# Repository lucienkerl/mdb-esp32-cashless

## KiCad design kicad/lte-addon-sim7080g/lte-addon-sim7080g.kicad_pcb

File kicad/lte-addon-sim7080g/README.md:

# LTE add-on module (SIM7080G) for the WROOM-1U board

Plug-in module that gives the [MDB ESP32-S3-WROOM-1U board](../mdb_slave_esp32s3-wroom-1u/)
an LTE-M / NB-IoT uplink. It sits on the mainboard's **J2** (1×6 JTAG socket) and
reuses the proven modem circuit of the [SIM7080G board](../mdb-slave-esp32s3-sim7080g/):
SIMCom SIM7080G, Nano-SIM, U.FL antenna connector.

## Status

- Revision **1.0**, not built yet — treat the first batch as a prototype.
- 4-layer board, 50 × 27.3 mm (with a 16 × 4 mm tab carrying the header).
- ERC: 1 known item (below). DRC: 0 errors, 0 warnings, 0 unconnected; schematic and PCB in sync.
- Fabrication files for JLCPCB in [`fab/`](fab/): gerber + drill zip, `BOM_JLCPCB.csv`, `CPL_JLCPCB.csv`.

## Connector (J1, male header on the bottom)

| J1 / mainboard J2 pin | ESP32-S3 | Function on the module |
|---|---|---|
| 1 | GPIO42 (MTMS) | DETECT — 10k pull-up to 3V3, so it reads HIGH when the module is plugged in |
| 2 | GPIO41 (MTDI) | PWRKEY — GPIO high turns Q3 on and pulls PWRKEY low (“press”) |
| 3 | GPIO40 (MTDO) | ESP TX → modem UART1_RXD (level shifter Q1) |
| 4 | GPIO39 (MTCK) | modem UART1_TXD → ESP RX (level shifter Q2) |
| 5 | GND | |
| 6 | +3V3 | modem supply (VBAT) via R1 |

The pin numbers are printed next to the header on the bottom silkscreen.

## Circuit

- **Supply**: VBAT is the mainboard's 3V3 rail through R1 (0 Ω, 1206), exactly like the
  SIM7080G board. SIM7080G accepts 2.7–4.8 V and only does LTE-M / NB-IoT (no 2G bursts),
  so the AP63201 on the mainboard (2 A) has enough headroom. C1 (220 µF low-ESR tantalum),
  C2 (100 µF), C3 (22 µF) and C4–C6 (100 nF / 33 pF / 10 pF) sit next to the VBAT pins and
  carry the TX bursts. Remove R1 and bridge it with an ammeter to measure the modem current.
  A local buck regulator from the MDB supply was considered and dropped: it does not fit next
  to the modem at this size, and an extra supply cable would not clear the case lid.
- **UART**: 3.3 V ↔ 1.8 V (VDD_EXT) level shifting with two MMBT3904 (Q1/Q2) and pull-ups
  R2–R5, the same topology as the SIM7080G board.
- **PWRKEY**: Q3 with R6 (4.7k base) and R7 (4.7k base-to-GND, keeps the modem off while
  GPIO41 floats during ESP reset). Polarity matches `MODEM_PWRKEY_INVERTED = 1`.
- **Nano-SIM**: JAE SF72S006, 22 Ω series resistors R12–R14, C7 on SIM_VDD.
- **Antenna**: 50 Ω line on F.Cu over the In1 ground plane (0.36 mm, JLC 4-layer stack-up),
  pi match R15 (0 Ω) + C8/C9 (not fitted), Hirose U.FL (J3). Use a U.FL → SMA bulkhead pigtail;
  the case needs a second SMA hole next to the WiFi antenna.
- **Status**: green network LED (D1, NETLIGHT via Q4), test points STATUS, VBAT, GND.
- GNSS and USB of the SIM7080G are not used.

## Assembly

- Solder a **1×6 male pin header on the bottom**, pins pointing down. On the mainboard J2
  takes a standard 8.5 mm female socket, which puts the module about 11 mm above the mainboard;
  the tallest part on top (SIM holder / modem) stays well under the 19 mm lid clearance.
- The outline keeps clear of the mainboard's tall parts (checked against their courtyards and
  silkscreen body outlines): about 0.6 mm to J1 (RFID cable), 0.4 mm to the I2C connector J3,
  1.0 mm to the custom-input terminal P2 (the top-right notch is for it), 0.85 mm to the screw terminals P3/P5/P6 along
  the bottom edge, 1.5 mm to the MDB connector. The buzzer sits under the module
  (3 mm tall, so 8 mm of air), which makes it a little quieter.
- H1/H2 (M2) take optional 11 mm nylon spacers resting on the mainboard; both land on bare
  board (H2 next to R18, clear of it with a 4 mm spacer).
- The modem pads carry via-in-pad ground vias: order **plugged / tented vias** (JLC “epoxy
  filled and capped”), otherwise solder wicks into them.
- J1, the test points and the mounting holes are not in the CPL (hand soldered / no part).

## Ordering at JLCPCB (PCB + assembly)

1. **PCB:** upload `fab/lte-addon-sim7080g_gerber_JLCPCB.zip`. Settings: 4 layers, 1.6 mm,
   impedance control with the JLC04161H-7628 stack-up (the RF line is sized for it), via
   covering **"Epoxy filled & capped"** (via-in-pad under the modem), surface finish ENIG
   recommended for the LCC modem pads.
2. **Assembly:** PCBA on the **top side** only, upload `fab/BOM_JLCPCB.csv` and
   `fab/CPL_JLCPCB.csv`. Every part carries its LCSC number. The SIM7080G (C2943992), the SIM
   holder (C2977286), the U.FL (C88373) and the 1210/tantalum caps are extended parts: check
   stock, or pre-order them into your JLC parts library before ordering.
3. In the placement preview check the rotation of U1 (pin-1 marker), C1 (tantalum polarity),
   D1 and the four SOT-23s; JLC's library origins sometimes differ from KiCad's.
4. C8/C9 (antenna match) stay unfitted. Solder J1 (1×6 male header, bottom side, pins down)
   by hand.

## Firmware

`mdb-slave-esp32s3` detects the module at boot: on the WROOM-1U board it reads GPIO42 with the
internal pull-down; HIGH selects GPIO39/40/41 as modem pins (`modem_set_pins()`) and the
normal cellular boot runs. Without the module the modem probe stays off, as before.

## Known ERC item

`power_pin_not_driven` on the SIM holder's VCC (J2 pin C1): SIM_VDD is driven by the modem's
SIM_VDD output, which the vendor symbol marks as a power pin. A PWR_FLAG would clash with that
output pin, so the item is left and only documented here.

## Regenerating

The design is generated from one source: [`scripts/design.py`](scripts/design.py) holds every part
and its pin-to-net map. Edit it, not the KiCad files. With KiCad 9 (e.g. the `kicad/kicad:9.0`
Docker image, which has `kicad-cli` and the pcbnew Python module):

```bash
cd kicad/lte-addon-sim7080g
docker run --rm -u 0 -v "$PWD":/p -w /p kicad/kicad:9.0 bash scripts/build.sh   # sch, place, route, DRC
docker run --rm -u 0 -v "$PWD":/p -w /p kicad/kicad:9.0 bash scripts/fab.sh     # gerbers, BOM, CPL, renders
```

| Script | Does |
|---|---|
| `gen_sch.py` | schematic from `design.py` |
| `gen_pcb.py place` / `finish` | outline, placement (mainboard coordinates, so J1 lands on J2), RF line, zones, silkscreen |
| `route.py` | grid router for all other nets plus ground fan-out and stitching |
| `fab.sh` / `jlc.py` | JLCPCB outputs |

The SIM7080G symbol and footprint (`lib/`) come from `../mdb-slave-esp32s3-sim7080g/SIM7080G.zip`.
The 3D renders show bare pads where the Docker image has no 3D models.

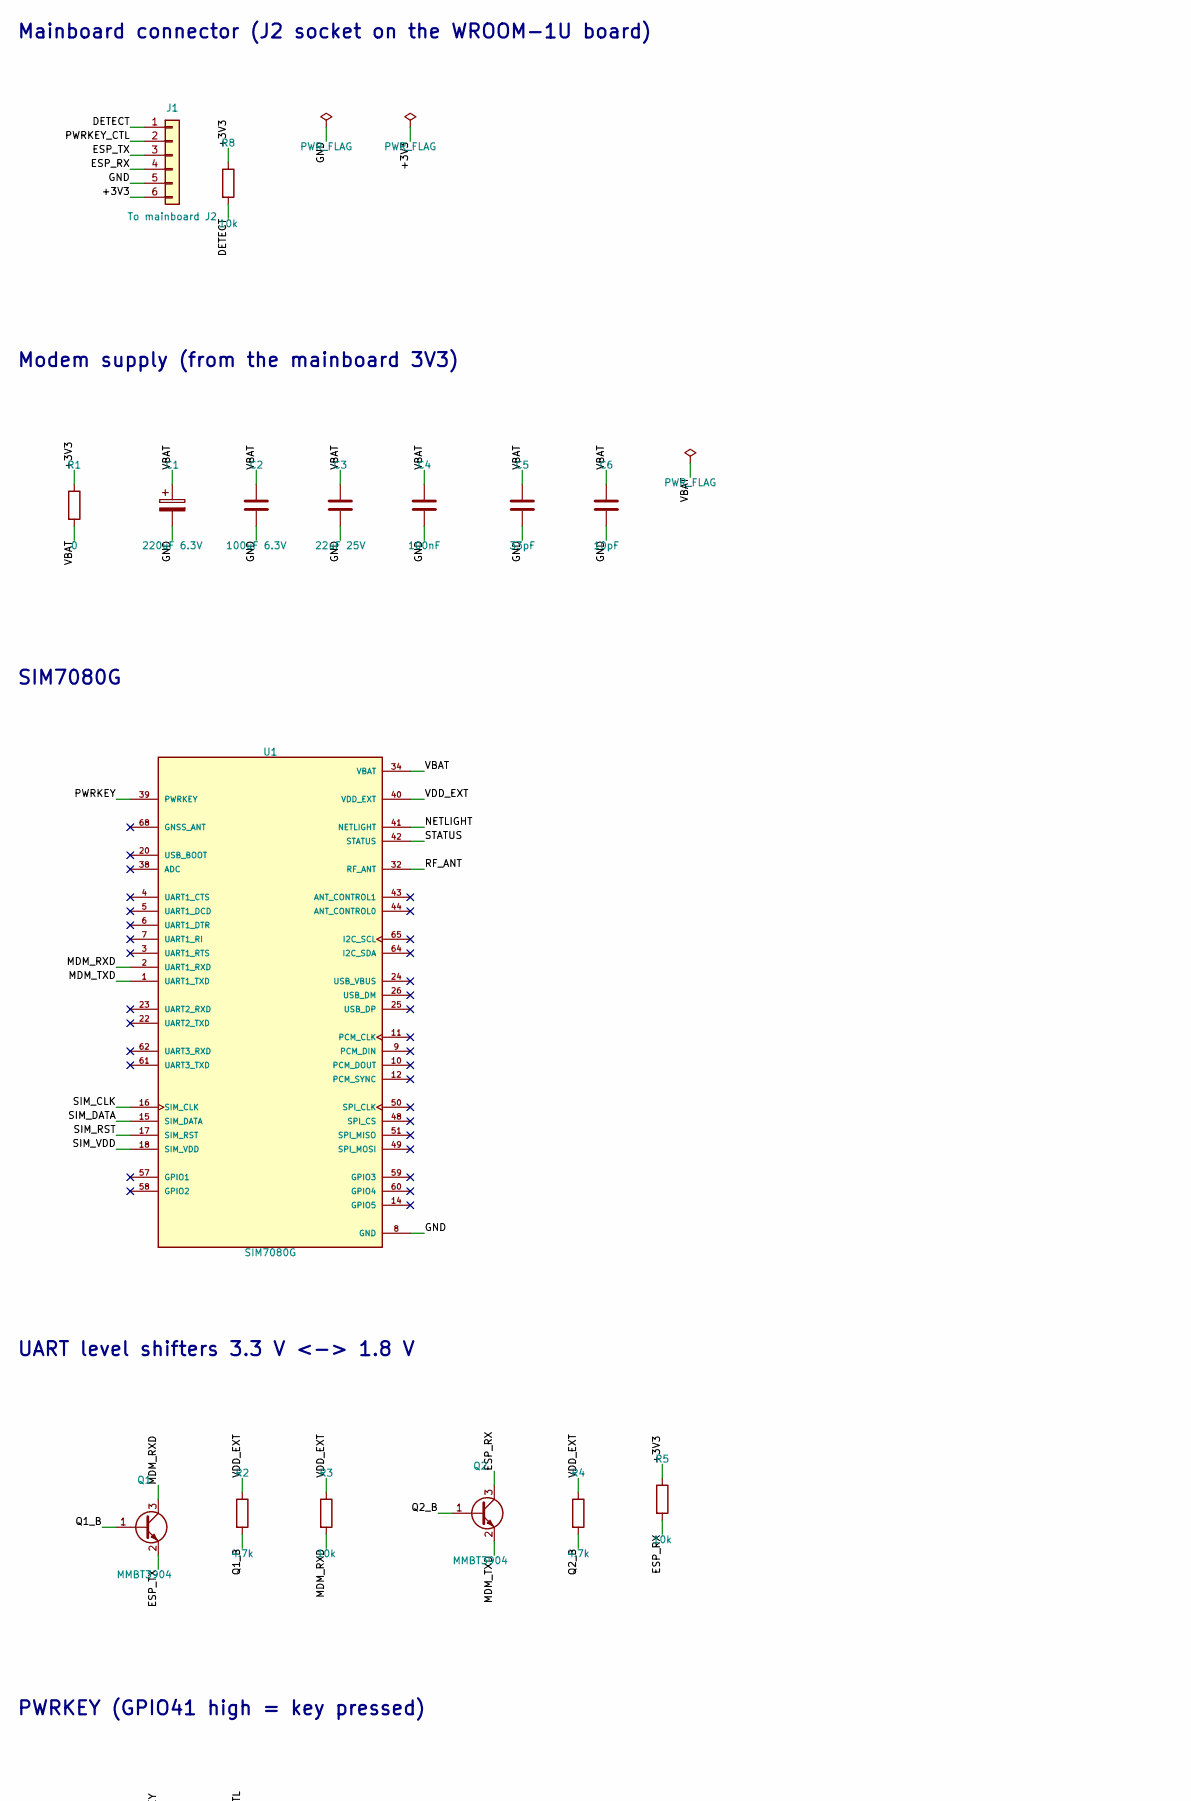
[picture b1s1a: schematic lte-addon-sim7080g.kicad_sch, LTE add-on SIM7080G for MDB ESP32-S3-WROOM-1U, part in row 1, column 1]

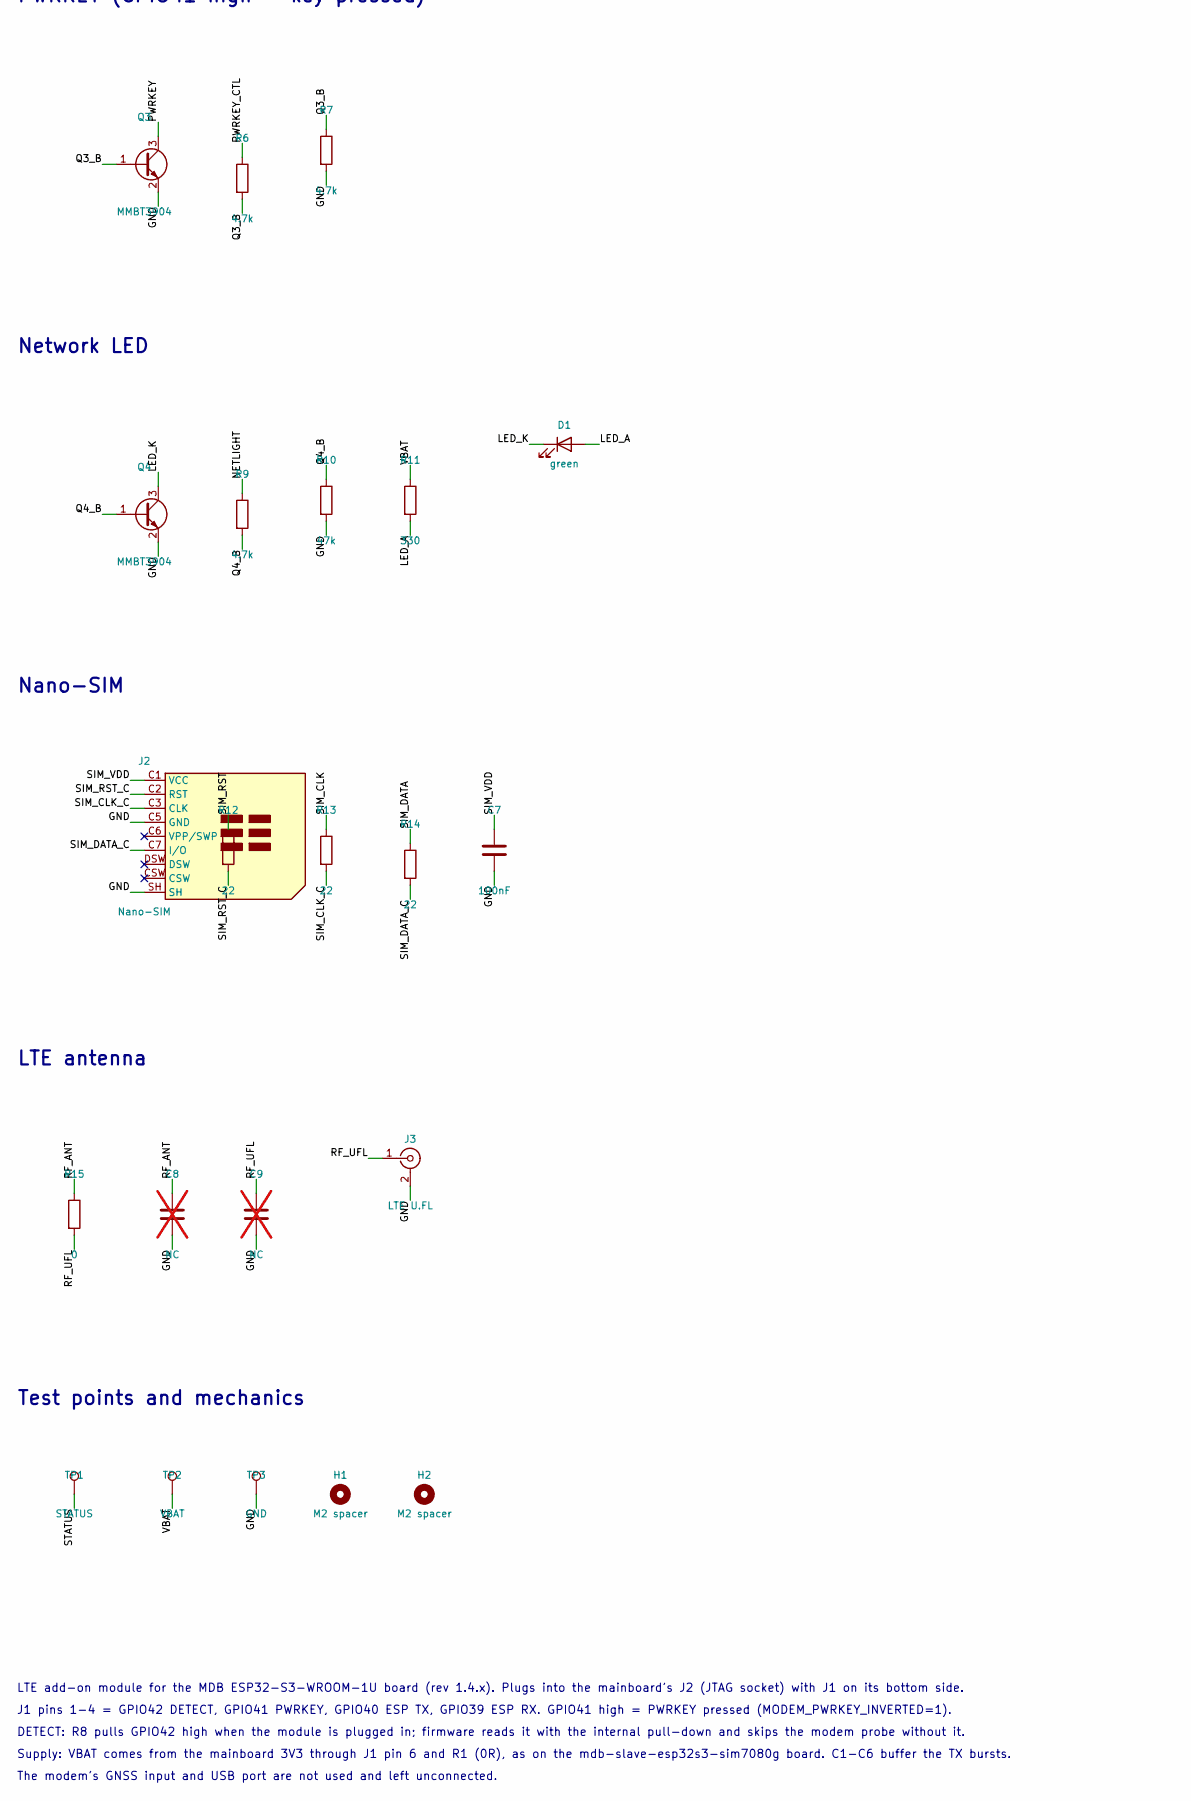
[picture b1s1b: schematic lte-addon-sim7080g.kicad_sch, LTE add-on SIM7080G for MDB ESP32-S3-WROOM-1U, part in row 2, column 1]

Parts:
C1: 220uF 6.3V; CP_EIA-3528-21_Kemet-B; MPN Kemet T520B227M006ATE070 (low ESR); LCSC C600584
C2: 100uF 6.3V; C_1210_3225Metric; LCSC C49066
C3: 22uF 25V; C_0805_2012Metric; LCSC C45783
C4, C7: 100nF; C_0603_1608Metric; LCSC C14663
C5: 33pF; C_0603_1608Metric; LCSC C1663
C6: 10pF; C_0603_1608Metric; LCSC C1634
C8, C9: NC; C_0603_1608Metric; not fitted
D1: green; LED_0603_1608Metric; LCSC C12624
H1, H2: M2 spacer; MountingHole_2.2mm_M2
J1: To mainboard J2; PinHeader_1x06_P2.54mm_Vertical; MPN Male pin header 1x6 2.54 mm, mounted on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
J2: Nano-SIM; JAE_SIM_Card_SF72S006; MPN JAE SF72S006VBDR2500; LCSC C2977286
J3: LTE U.FL; U.FL_Hirose_U.FL-R-SMT-1_Vertical; MPN Hirose U.FL-R-SMT-1; LCSC C88373
Q1, Q2, Q3, Q4: MMBT3904; SOT-23; LCSC C20526
R1: 0; R_1206_3216Metric; LCSC C17888
R2, R4, R6, R7, R9: 4.7k; R_0603_1608Metric; LCSC C23162
R3, R5, R8: 10k; R_0603_1608Metric; LCSC C25804
R10: 47k; R_0603_1608Metric; LCSC C25819
R11: 330; R_0603_1608Metric; LCSC C23138
R12, R13, R14: 22; R_0603_1608Metric; LCSC C23345
R15: 0; R_0603_1608Metric; LCSC C21189
TP1: STATUS; TestPoint_Pad_D1.0mm
TP2: VBAT; TestPoint_Pad_D1.0mm
TP3: GND; TestPoint_Pad_D1.0mm
U1: SIM7080G; XCVR_SIM7080G; MPN SIMCom SIM7080G; LCSC C2943992

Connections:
/+3V3: J1.6, R1.1, R5.1, R8.1
/DETECT: J1.1, R8.2
/ESP_RX: J1.4, Q2.3 (C), R5.2
/ESP_TX: J1.3, Q1.2 (E)
/LED_A: D1.2 (A), R11.2
/LED_K: D1.1 (K), Q4.3 (C)
/MDM_RXD: Q1.3 (C), R3.2, U1.2 (UART1_RXD)
/MDM_TXD: Q2.2 (E), U1.1 (UART1_TXD)
/NETLIGHT: R9.1, U1.41 (NETLIGHT)
/PWRKEY: Q3.3 (C), U1.39 (PWRKEY)
/PWRKEY_CTL: J1.2, R6.1
/Q1_B: Q1.1 (B), R2.2
/Q2_B: Q2.1 (B), R4.2
/Q3_B: Q3.1 (B), R6.2, R7.1
/Q4_B: Q4.1 (B), R9.2, R10.1
/RF_ANT: C8.1, R15.1, U1.32 (RF_ANT)
/RF_UFL: C9.1, J3.1 (In), R15.2
/SIM_CLK: R13.1, U1.16 (SIM_CLK)
/SIM_CLK_C: J2.C3 (CLK), R13.2
/SIM_DATA: R14.1, U1.15 (SIM_DATA)
/SIM_DATA_C: J2.C7 (I/O), R14.2
/SIM_RST: R12.1, U1.17 (SIM_RST)
/SIM_RST_C: J2.C2 (RST), R12.2
/SIM_VDD: C7.1, J2.C1 (VCC), U1.18 (SIM_VDD)
/STATUS: TP1.1, U1.42 (STATUS)
/VDD_EXT: R2.1, R3.1, R4.1, U1.40 (VDD_EXT)
GND: C1.2, C2.2, C3.2, C4.2, C5.2, C6.2, C7.2, C8.2, C9.2, J1.5, J2.C5 (GND), J2.SH, J3.2 (Ext), Q3.2 (E), Q4.2 (E), R7.2, R10.2, TP3.1, U1.8 (GND), U1.13 (GND), U1.19 (GND), U1.21 (GND), U1.27 (GND), U1.30 (GND), U1.31 (GND), U1.33 (GND), U1.36 (GND), U1.37 (GND), U1.45 (GND), U1.63 (GND), U1.66 (GND), U1.67 (GND), U1.69 (GND), U1.70 (GND), U1.71 (GND), U1.72 (GND), U1.73 (GND), U1.74 (GND), U1.75 (GND), U1.76 (GND), U1.77 (GND)
VBAT: C1.1, C2.1, C3.1, C4.1, C5.1, C6.1, R1.2, R11.1, TP2.1, U1.34 (VBAT), U1.35 (VBAT)

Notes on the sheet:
Mainboard connector (J2 socket on the WROOM-1U board)
Modem supply (from the mainboard 3V3)
SIM7080G
UART level shifters 3.3 V <-> 1.8 V
PWRKEY (GPIO41 high = key pressed)
Network LED
Nano-SIM
LTE antenna
Test points and mechanics
LTE add-on module for the MDB ESP32-S3-WROOM-1U board (rev 1.4.x). Plugs into the mainboard's J2 (JTAG socket) with J1 on its bottom side.
J1 pins 1-4 = GPIO42 DETECT, GPIO41 PWRKEY, GPIO40 ESP TX, GPIO39 ESP RX. GPIO41 high = PWRKEY pressed (MODEM_PWRKEY_INVERTED=1).
DETECT: R8 pulls GPIO42 high when the module is plugged in; firmware reads it with the internal pull-down and skips the modem probe without it.
Supply: VBAT comes from the mainboard 3V3 through J1 pin 6 and R1 (0R), as on the mdb-slave-esp32s3-sim7080g board. C1-C6 buffer the TX bursts.
The modem's GNSS input and USB port are not used and left unconnected.

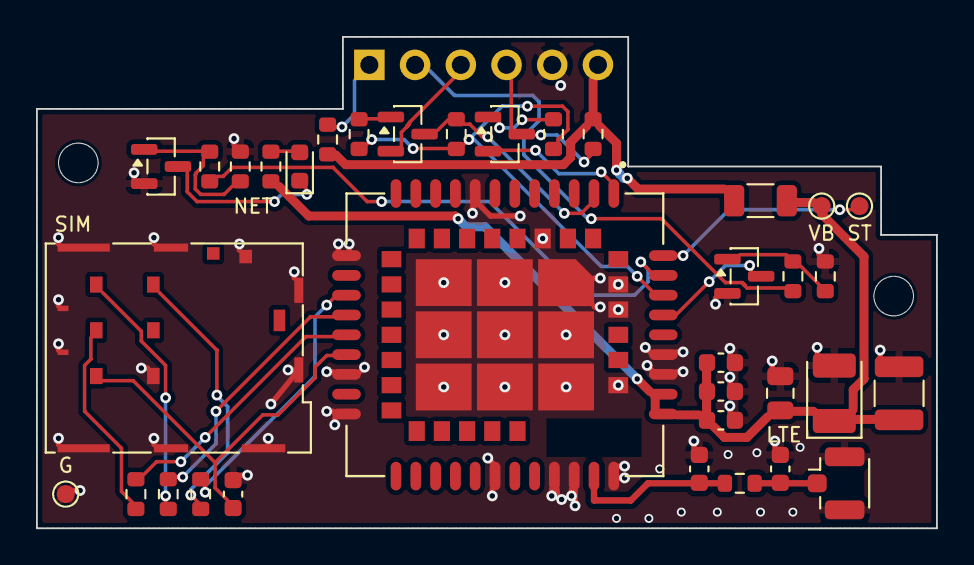
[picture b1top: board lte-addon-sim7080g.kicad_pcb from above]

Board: 4 copper layers, 50.0 x 27.3 mm, 38 parts (1 on the bottom side), 28 nets.

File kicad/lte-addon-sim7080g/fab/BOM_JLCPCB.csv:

Comment,Designator,Footprint,LCSC Part #,MPN / note,Quantity
220uF 6.3V,C1,CP_EIA-3528-21_Kemet-B,C600584,Kemet T520B227M006ATE070 (low ESR),1
100uF 6.3V,C2,C_1210_3225Metric,C49066,,1
22uF 25V,C3,C_0805_2012Metric,C45783,,1
100nF,"C4,C7",C_0603_1608Metric,C14663,,2
33pF,C5,C_0603_1608Metric,C1663,,1
10pF,C6,C_0603_1608Metric,C1634,,1
green,D1,LED_0603_1608Metric,C12624,,1
Nano-SIM,J2,JAE_SIM_Card_SF72S006,C2977286,JAE SF72S006VBDR2500,1
LTE U.FL,J3,U.FL_Hirose_U.FL-R-SMT-1_Vertical,C88373,Hirose U.FL-R-SMT-1,1
MMBT3904,"Q1,Q2,Q3,Q4",SOT-23,C20526,,4
0,R1,R_1206_3216Metric,C17888,,1
4.7k,"R2,R4,R6,R7,R9",R_0603_1608Metric,C23162,,5
10k,"R3,R5,R8",R_0603_1608Metric,C25804,,3
47k,R10,R_0603_1608Metric,C25819,,1
330,R11,R_0603_1608Metric,C23138,,1
22,"R12,R13,R14",R_0603_1608Metric,C23345,,3
0,R15,R_0603_1608Metric,C21189,,1
SIM7080G,U1,XCVR_SIM7080G,C2943992,SIMCom SIM7080G,1

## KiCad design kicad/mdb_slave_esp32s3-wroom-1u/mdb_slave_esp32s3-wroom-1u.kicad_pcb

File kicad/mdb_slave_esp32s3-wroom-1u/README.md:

# MDB ESP32-S3 Cashless Module

Custom PCB adding cashless payment and telemetry to vending machines via the **MDB (Multi-Drop Bus)** protocol. Built around an **ESP32-S3-WROOM-1U** module with external antenna. Designed in KiCad 10.

Target platform: any vending machine equipped with an MDB bus. Backend (Supabase + MQTT + Nuxt, Dockerized) is out of scope for this repo.

Base reference: [lucienkerl/mdb-esp32-cashless](https://github.com/lucienkerl/mdb-esp32-cashless).

## Status

- Schematic: complete — ERC has 4 minor housekeeping items left (floating power symbols / an
  unconnected test pad, no real connectivity impact)
- PCB layout: routed, 4-layer board, 149.8 × 38.5 mm — schematic and PCB are in sync (all
  references renumbered and re-synced in rev1.4, including the previously-orphaned 1-Wire
  pull-up R4)
- Revision: **1.4.1** (R26/R28 changed from 10KΩ to 1KΩ)
- Gerbers in `gerber_to_order/` (JLCPCB, PCBWay) reflect the current board

## Overview

The board sits between the vending machine's MDB bus and a cashless payment terminal / telemetry stack. It reads and drives the machine's MDB peripherals, exposes auxiliary sensor and actuator interfaces (1-Wire, I2C, relays, custom digital inputs), and connects to WiFi for backend communication.

Key design decisions:

- **ESP32-S3-WROOM-1U-N16R2** module (16MB flash / 2MB PSRAM) with external u.FL antenna, chosen over a bare ESP32-S3 die because vending machine enclosures are often metal and block internal WiFi.
- **4-layer PCB**, for a dedicated ground/power plane structure and better EMI control around the switching regulator and MDB interface.
- All field connectors placed at the board edge for easy wiring and to fit inside a 3D-printed enclosure.
- Physical separation between the MDB (isolated, high-voltage) side and the logic side, matching the optocoupler isolation barrier in the schematic.

## Functional blocks

**MCU — U1**
ESP32-S3-WROOM-1U-N16R2, with EN/BOOT reset circuit (buttons B1/B2, pull-ups R1/R2/R10, decoupling C1–C3). Onboard WS2812B-compatible RGB status LED (LED1, driven by GPIO21).

**Power**
- F2: PTC resettable fuse on the incoming MDB-side supply
- U8: AP63201WU-7 buck converter, input 3.8V–32V, output 3.3V — **adjustable-output part** (rev1.4, replaces the fixed-output AP63203QWU-7), set by an external feedback divider: R23 (196kΩ, top) / R24 (62kΩ, bottom), with C19 (100pF) as feed-forward capacitor across R23
- C6 (10µF input), C7 (100nF bootstrap), C8/C9 (2×22µF output), L1 (3.3µH inductor)
- Switching loop (U8–L1–output) kept as compact as possible — primary EMI concern

**USB-C — USBC1**
USB 2.0 receptacle for programming/debug, with D6 Schottky diode against VBUS backfeed and R21/R22 CC pull-downs.

**MDB interface — H1**
2×3 connector. Galvanically isolated via U5/U6 (TLP785 optocouplers, DIP-4) on TX (GPIO4) and RX (GPIO5), with D2/D3 and associated pull-up/series resistors. F1 is the PTC resettable fuse on the incoming MDB-side supply.

**Relay outputs — P8, P9** *(added rev1.3)*
Two 15A-class SPDT relays (K2, K3 — SRD-03VDC-SL-C, 3V coil on the +3V3 rail), each output exposed as a 3-pin COM/NO/NC screw terminal. Each coil is driven low-side by an MMBT3904 transistor (Q2/Q3) with a 1N4148WS flyback diode (D4/D5), itself switched through a TLP785 optocoupler (U3/U4, SMD-4) for GPIO isolation:
- P8: Relay #1 — K2 / Q2 / U3, driven from GPIO1
- P9: Relay #2 — K3 / Q3 / U4, driven from GPIO2

⚠️ Note (intentional design choice): with the current TLP785 pull-up/pull-down arrangement, drive logic is inverted (GPIO low, or floating at boot, = relay energized; GPIO high = relay de-energized). This matches this board's firmware. If you reuse this design, or adapt a different firmware to it, update the GPIO drive logic accordingly — or flip the pull-up/pull-down if a fail-safe de-energized boot default is required.

**1-Wire buses — P4, P5, P6**
Two 1-Wire interfaces plus a spare/parallel header, each with a pull-up resistor:
- P6: bus #1 (GPIO15)
- P5: bus #2 (GPIO16)
- P4: spare header on bus #1 (GPIO15)

**Custom digital inputs — P1, P2, P3**
Three screw-terminal inputs with pull-up resistors: P1 (GPIO6), P2 (GPIO17), P3 (GPIO18).

**I2C — J3**
JST XH 1×4 connector with pull-ups, SCL on GPIO11, SDA on GPIO10.

**Debug / programming**
- J1: UART debug header (1×6) — EN, TXD, RXD, IO0, GND, +3V3
- J2: JTAG header (1×6) — MTMS, MTDI, MTDO, MTCk, GND, +3V3

**Other**
- TH1: NTC thermistor input (GPIO7)
- BUZZER1: buzzer, driven by GPIO12 through Q1
- H2–H5: mounting holes
- H6–H10: test/probe pads (H8 taps the WS2812B LED1 data-out, H10 the buzzer driver)
- GPIO3: reserved for firmware-based PCB/board detection

## Connectors summary

| Ref | Function | Type |
|---|---|---|
| USBC1 | USB-C (program/debug) | USB2.0 16P receptacle |
| J1 | UART debug | 1×6 pin header |
| J2 | JTAG | 1×6 pin header |
| J3 | I2C | 1×4 JST XH |
| P1, P2, P3 | Custom digital inputs (×3) | 3-pin screw terminal, 5.08mm |
| P4, P5, P6 | 1-Wire buses (bus #1 spare, bus #2, bus #1) | 3-pin screw terminal, 5.08mm |
| P8 | Relay #1 output (COM/NO/NC) | 3-pin screw terminal, 5.08mm |
| P9 | Relay #2 output (COM/NO/NC) | 3-pin screw terminal, 5.08mm |
| H1 | MDB bus | 2×3 connector, isolated |

## Repository structure

```
mdb_slave_esp32s3-wroom-1u/
├── mdb_slave_esp32s3-wroom-1u.kicad_pro   KiCad project
├── mdb_slave_esp32s3-wroom-1u.kicad_sch   Schematic
├── mdb_slave_esp32s3-wroom-1u.kicad_pcb   PCB layout (routed, rev 1.4.1)
├── LICENSE                                CERN-OHL-S v2
├── gerber_to_order/                       Fabrication Gerbers per vendor (JLCPCB, PCBWay) — versioned
├── bom/ibom.html                          Interactive BOM (InteractiveHtmlBom export) — versioned
└── production/                            BOM, CPL, netlist (generated locally, not versioned)
```

The `.kicad_pro` / `.kicad_sch` / `.kicad_pcb` files, this README, `LICENSE`, `gerber_to_order/`,
and `bom/ibom.html` are version-controlled — see `.gitignore`.

## Browsing the board without KiCad

Open `bom/ibom.html` in any browser for an interactive BOM: it highlights each component on the
PCB (top/bottom view) when selected, lists references/values/footprints, and supports search and
filtering — useful for assembly checks or reviewing the design without installing KiCad.

## Tools

- KiCad 10.0.4
- JLCPCB / PCBWay for fabrication, assembly, and component sourcing

## License

[CERN-OHL-S v2](https://choosealicense.com/licenses/cern-ohl-s-2.0/) — see `LICENSE`.

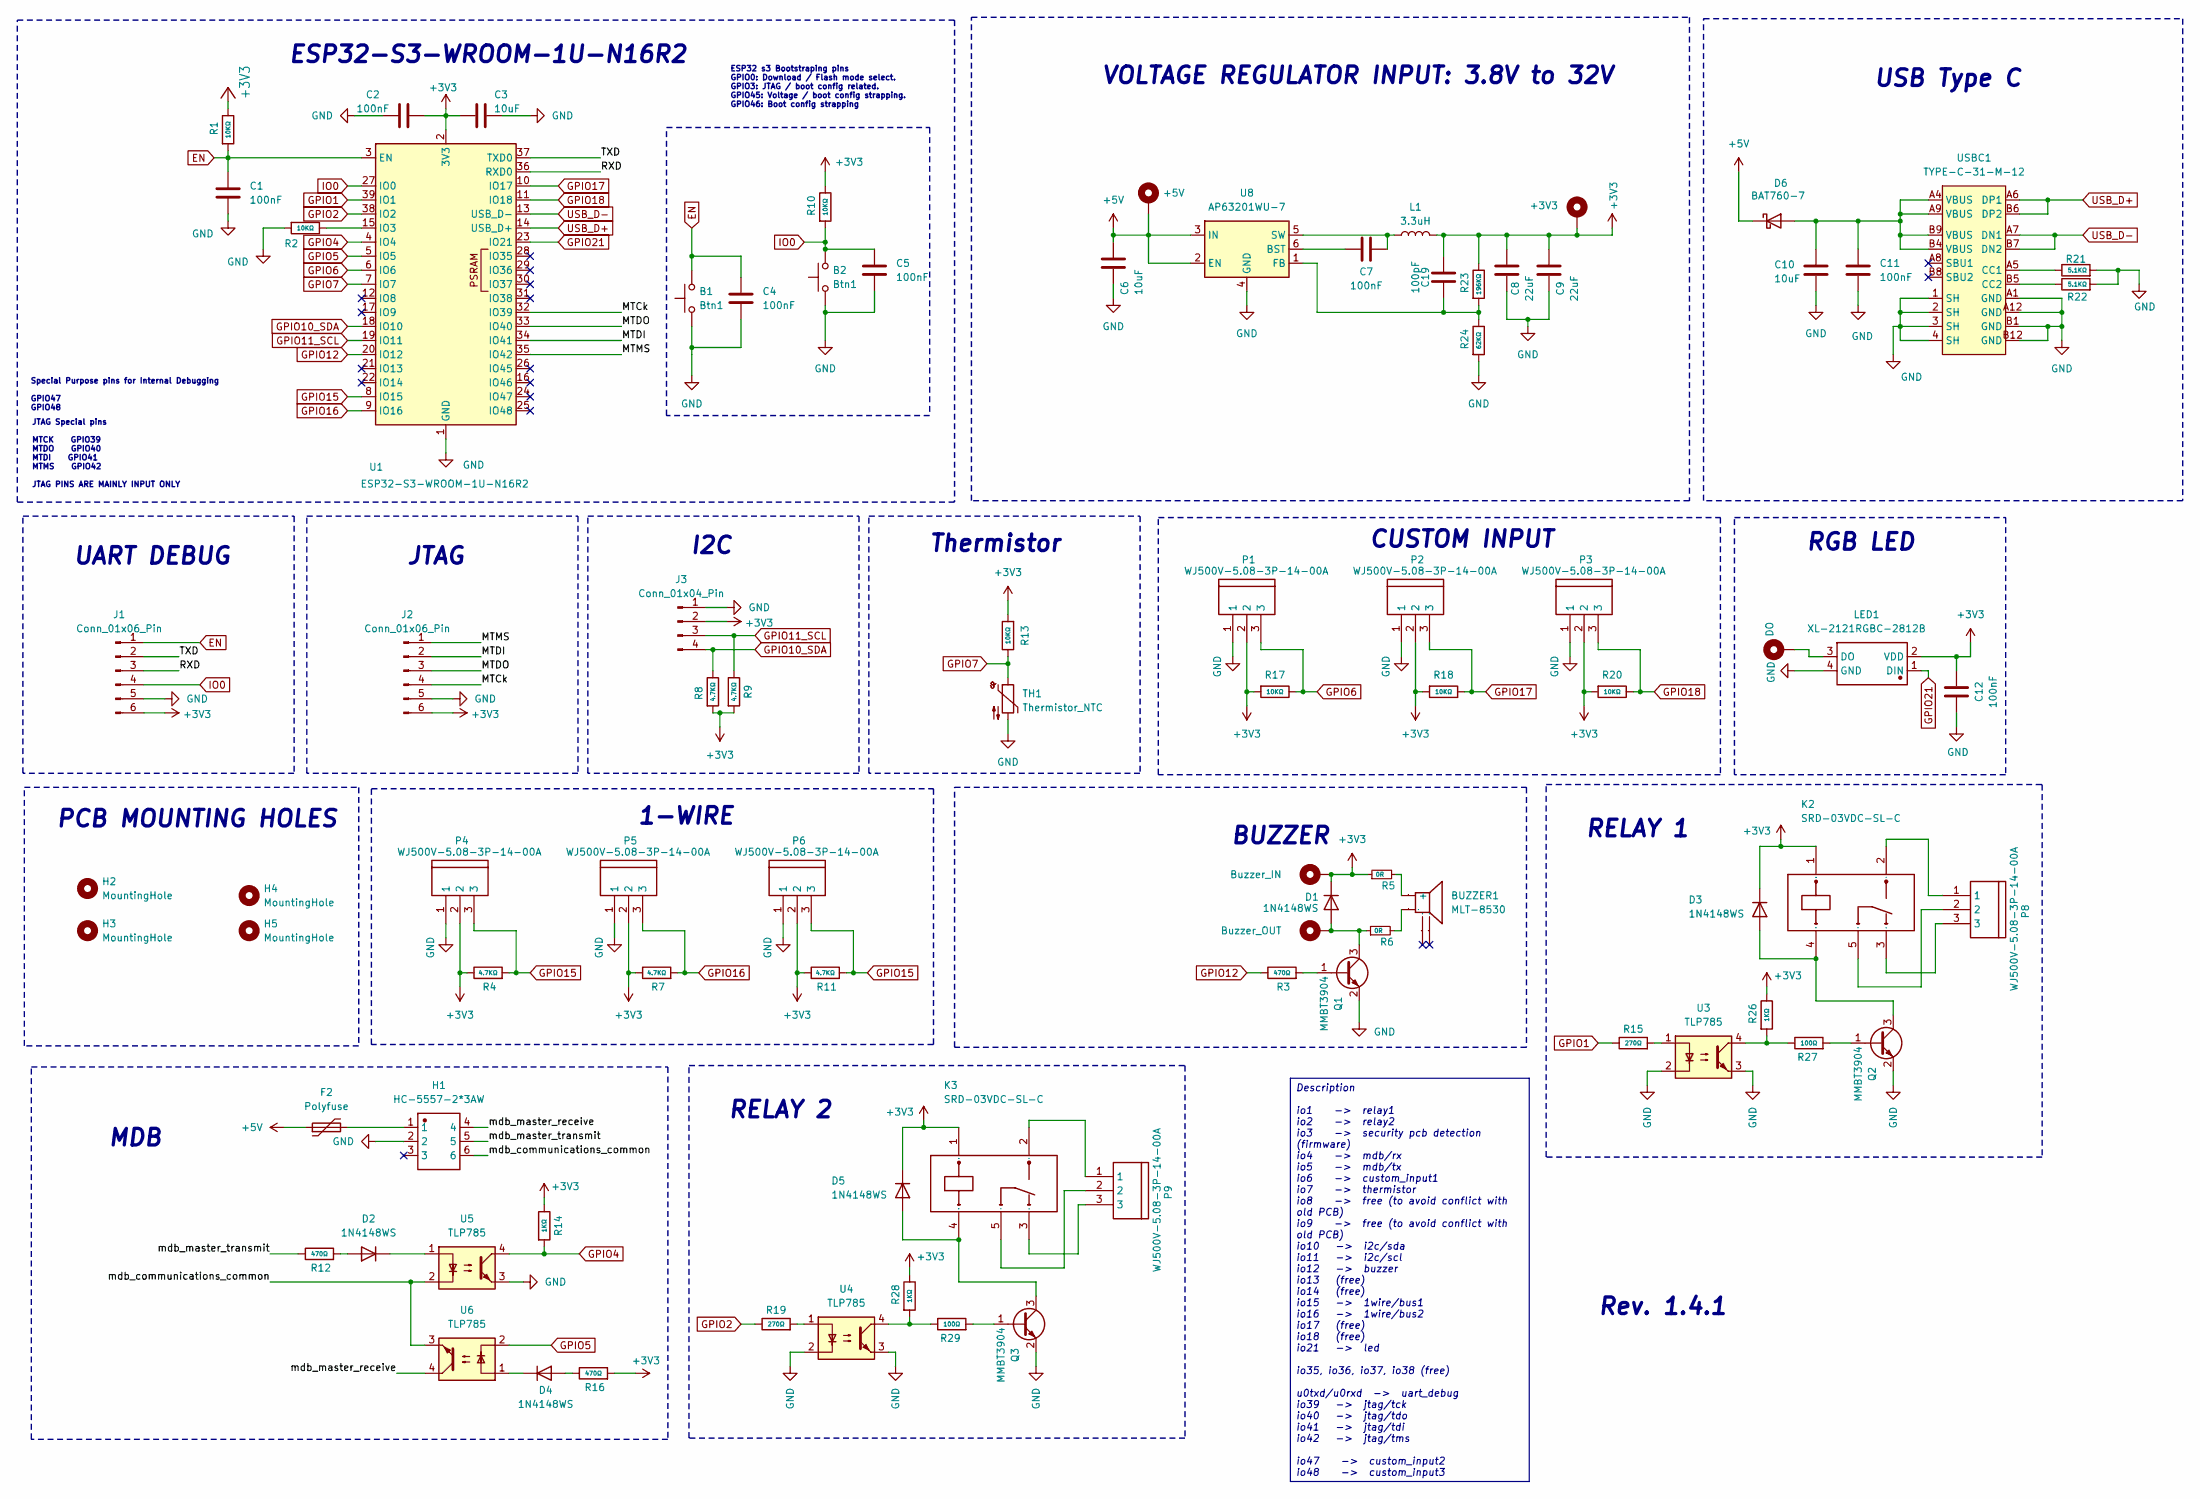
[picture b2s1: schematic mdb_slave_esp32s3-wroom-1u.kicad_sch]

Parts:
B1, B2: Btn1; KEY-SMD_B3U-1000PM; MFR.Part # B3U-1000P; LCSC C231329
BUZZER1: MLT-8530; BUZ-SMD_4P-L8.5-W8.5-P8.50-BR_C94599; MFR.Part # MLT-8530; LCSC C94599
C1, C2, C4, C5, C7, C11, C12: 100nF; C_0603_1608Metric; MFR.Part # CC0603KRX7R9BB104; LCSC C14663
C3, C6, C10: 10uF; C_0603_1608Metric; MFR.Part # CL10A106KP8NNNC; LCSC C19702
C8, C9: 22uF; C_0603_1608Metric; MFR.Part # CL10A226MQ8NRNC; LCSC C59461
C19: 100pF; C_0603_1608Metric; MFR.Part # CL10C101JB8NNNC; LCSC C14858
D1, D2, D3, D4, D5: 1N4148WS; D_SOD-323; MFR.Part # 1N4148WS; LCSC C2128
D6: BAT760-7; D_SOD-323; MFR.Part # BAT760-7; LCSC C27636120
F2: Polyfuse; C_1812_4532Metric; MFR.Part # 1812L110/33GR; LCSC C7542972
H1: HC-5557-2*3AW; CONN-TH_6P-P4.20-S5.50_5557-2X3AW_C2845788; MFR.Part # HC-5557-2*3AW; LCSC C2845788
H2, H3, H4, H5: MountingHole; MountingHole_2.7mm_M2.5_ISO7380
H6: +5V; TestPoint_Pad_D1.0mm
H7: +3V3; TestPoint_Pad_D1.0mm
H8: DO; TestPoint_Pad_D1.0mm
H9: Buzzer_IN; TestPoint_Pad_D1.0mm
H10: Buzzer_OUT; TestPoint_Pad_D1.0mm
J1, J2: Conn_01x06_Pin; PinSocket_1x06_P2.54mm_Vertical; LCSC C37208
J3: Conn_01x04_Pin; JST_XH_B4B-XH-A_1x04_P2.50mm_Vertical; MFR.Part # B4B-XH-A(LF)(SN); LCSC C144395
K2, K3: SRD-03VDC-SL-C; RELAY-TH_SRD-XXVDC-XL-C_C24585; MFR.Part # SRD-03VDC-SL-C; LCSC C24585
L1: 3.3uH; L_0603_1608Metric; MFR.Part # SDFL1608S6R8KTF; LCSC C75929
LED1: XL-2121RGBC-2812B; LED-SMD_4P-L2.1-W2.1-BR_XL-2121RGBC-WS2812B_C5349957; MFR.Part # XL-2121RGBC-2812B; LCSC C5349957
P1, P2, P3, P4, P5, P6, P8, P9: WJ500V-5.08-3P-14-00A; CONN-TH_3P-P5.00_WJ500V-5.08-3P_C72334; MFR.Part # WJ500V-5.08-03P-14-00A; LCSC C72334
Q1, Q2, Q3: MMBT3904; SOT-23; MFR.Part # MMBT3904; LCSC C916374
R1, R2, R10, R13, R17, R18, R20: 10KΩ; R_0603_1608Metric; MFR.Part # 0603WAF1002T5E; LCSC C25804
R3, R12, R16: 470Ω; R_0603_1608Metric; MFR.Part # 0603WAF4700T5E; LCSC C23179
R4, R7, R8, R9, R11: 4.7KΩ; R_0603_1608Metric; MFR.Part # 0603WAF4701T5E; LCSC C23162
R5, R6: 0R; R_0603_1608Metric_Pad0.98x0.95mm_HandSolder; MFR.Part # 0603WAF0000T5E; LCSC C21189
R14, R26, R28: 1KΩ; R_0603_1608Metric; MFR.Part # RC0603JR-071KL; LCSC C14676
R15, R19: 270Ω; R_0603_1608Metric; MFR.Part # 0603WAF2700T5E; LCSC C22966
R21, R22: 5.1KΩ; R_0603_1608Metric; MFR.Part # 0603WAF5101T5E; LCSC C23186
R23: 196KΩ; R_0603_1608Metric; MFR.Part # 0603WAF1963T5E; LCSC C22930
R24: 62KΩ; R_0603_1608Metric; MFR.Part # 0603WAF6202T5E; LCSC C23221
R27, R29: 100Ω; R_0603_1608Metric; MFR.Part # 0603WAF1000T5E; LCSC C22775
TH1: Thermistor_NTC; C_0603_1608Metric_Pad1.08x0.95mm_HandSolder; MFR.Part # NCP18XH103F03RB; LCSC C13564
U1: ESP32-S3-WROOM-1U-N16R2; WIRELM-SMD_ESP32-S3-WROOM-1U_C3013945; MFR.Part # ESP32-S3-WROOM-1U-N16R2; LCSC C3013945
U3, U4, U5, U6: TLP785; SMD-4_L4.6-W6.5-P2.54-LS10.2-BR_C45445; MFR.Part # TLP785(GB-TP6,F; LCSC C45445
U8: AP63201WU-7; TSOT-23-6; MFR.Part # AP63201WU-7; LCSC C2071044
USBC1: TYPE-C-31-M-12; USB-C_SMD-TYPE-C-31-M-12; MFR.Part # TYPE-C-31-M-12; LCSC C165948

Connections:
+3V3: C2.2, C3.2, C8.2, C9.2, C12.2, C19.1, D1.1 (K), D3.1 (K), D5.1 (K), H7.1, H9.1, J1.6, J2.6, J3.2, K2.1, K3.1, L1.2, LED1.2 (VDD), P1.2, P2.2, P3.2, P4.2, P5.2, P6.2, R1.1, R4.1, R5.1, R7.1, R8.2, R9.2, R10.1, R11.1, R13.2, R14.1, R16.2, R17.2, R18.2, R20.2, R23.1, R26.1, R28.1, U1.2 (3V3)
+5V: C6.1, D6.1 (K), F2.1, H6.1, U8.2 (EN), U8.3 (IN)
/MTCk: J2.4, U1.32 (IO39)
/MTDI: J2.2, U1.34 (IO41)
/MTDO: J2.3, U1.33 (IO40)
/MTMS: J2.1, U1.35 (IO42)
/RXD: J1.3, U1.36 (RXD0)
/TXD: J1.2, U1.37 (TXD0)
/mdb_communications_common: H1.6, U5.2, U6.3
/mdb_master_receive: H1.4, U6.4
/mdb_master_transmit: H1.5, R12.1
EN: B1.2, C1.1, C4.1, J1.1, R1.2, U1.3 (EN)
GND: B1.1, B2.1, C1.2, C2.1, C3.1, C4.2, C5.2, C6.2, C8.1, C9.1, C10.2, C11.2, C12.1, H1.2, J1.5, J2.5, J3.1, LED1.4 (GND), P1.1, P2.1, P3.1, P4.1, P5.1, P6.1, Q1.2 (E), Q2.2 (E), Q3.2 (E), R2.2, R21.2, R22.2, R24.2, TH1.2, U1.1 (GND), U1.40 (GND), U1.41 (GND), U3.2, U3.3, U4.2, U4.3, U5.3, U8.4 (GND), USBC1.1 (SH), USBC1.2 (SH), USBC1.3 (SH), USBC1.4 (SH), USBC1.A1 (GND), USBC1.A12 (GND), USBC1.B1 (GND), USBC1.B12 (GND)
GPIO1: R15.1, U1.39 (IO1)
GPIO2: R19.1, U1.38 (IO2)
GPIO4: R14.2, U1.4 (IO4), U5.4
GPIO5: U1.5 (IO5), U6.2
GPIO6: P1.3, R17.1, U1.6 (IO6)
GPIO7: R13.1, TH1.1, U1.7 (IO7)
GPIO10_SDA: J3.4, R8.1, U1.18 (IO10)
GPIO11_SCL: J3.3, R9.1, U1.19 (IO11)
GPIO12: R3.1, U1.20 (IO12)
GPIO15: P4.3, P6.3, R4.2, R11.2, U1.8 (IO15)
GPIO16: P5.3, R7.2, U1.9 (IO16)
GPIO17: P2.3, R18.1, U1.10 (IO17)
GPIO18: P3.3, R20.1, U1.11 (IO18)
GPIO21: LED1.1 (DIN), U1.23 (IO21)
IO0: B2.2, C5.1, J1.4, R10.2, U1.27 (IO0)
unnamed: BUZZER1.1 (+), R5.2
unnamed: BUZZER1.2, R6.2
unnamed: D1.2 (A), H10.1, Q1.3 (C), R6.1
unnamed: D2.2 (A), R12.2
unnamed: D2.1 (K), U5.1
unnamed: D3.2 (A), K2.4, Q2.3 (C)
unnamed: D4.2 (A), R16.1
unnamed: D4.1 (K), U6.1
unnamed: D5.2 (A), K3.4, Q3.3 (C)
unnamed: C10.1, C11.1, D6.2 (A), USBC1.A4 (VBUS), USBC1.A9 (VBUS), USBC1.B4 (VBUS), USBC1.B9 (VBUS)
unnamed: F2.2, H1.1
unnamed: K2.2, P8.1
unnamed: K2.3, P8.3
unnamed: K2.5, P8.2
unnamed: K3.2, P9.1
unnamed: K3.3, P9.3
unnamed: K3.5, P9.2
unnamed: H8.1, LED1.3 (DO)
unnamed: Q1.1 (B), R3.2
unnamed: Q2.1 (B), R27.2
unnamed: Q3.1 (B), R29.2
unnamed: R15.2, U3.1
unnamed: R19.2, U4.1
unnamed: R26.2, R27.1, U3.4
unnamed: R28.2, R29.1, U4.4
unnamed: R2.1, U1.15 (IO3)
unnamed: C7.1, U8.6 (BST)
unnamed: C19.2, R23.2, R24.1, U8.1 (FB)
unnamed: C7.2, L1.1, U8.5 (SW)
unnamed: R21.1, USBC1.A5 (CC1)
unnamed: R22.1, USBC1.B5 (CC2)
USB_D+: U1.14 (USB_D+), USBC1.A6 (DP1), USBC1.B6 (DP2)
USB_D-: U1.13 (USB_D-), USBC1.A7 (DN1), USBC1.B7 (DN2)

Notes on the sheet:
MDB
Special Purpose pins for Internal Debugging GPIO47 GPIO48
RGB LED
RELAY 2
PCB MOUNTING HOLES
1-WIRE
Thermistor
CUSTOM INPUT
Rev. 1.4.1
UART DEBUG
I2C
USB Type C
BUZZER
ESP32-S3-WROOM-1U-N16R2
RELAY 1
JTAG
JTAG Special pins MTCK GPIO39 MTDO GPIO40 MTDI GPIO41 MTMS GPIO42 JTAG PINS ARE MAINLY INPUT ONLY
ESP32 s3 Bootstraping pins GPIO0: Download / Flash mode select. GPIO3: JTAG / boot config related. GPIO45: Voltage / boot config strapping. GPIO46: Boot config strapping
VOLTAGE REGULATOR INPUT: 3.8V to 32V
Description io1 -> relay1 io2 -> relay2 io3 -> security pcb detection (firmware) io4 -> mdb/rx io5 -> mdb/tx io6 -> custom_input1 io7 -> thermistor io8 -> free (to avoid conflict with old PCB) io9 -> free (to avoid conflict with old PCB) io10 -> i2c/sda io11 -> i2c/scl io12 -> buzzer io13 (free) io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

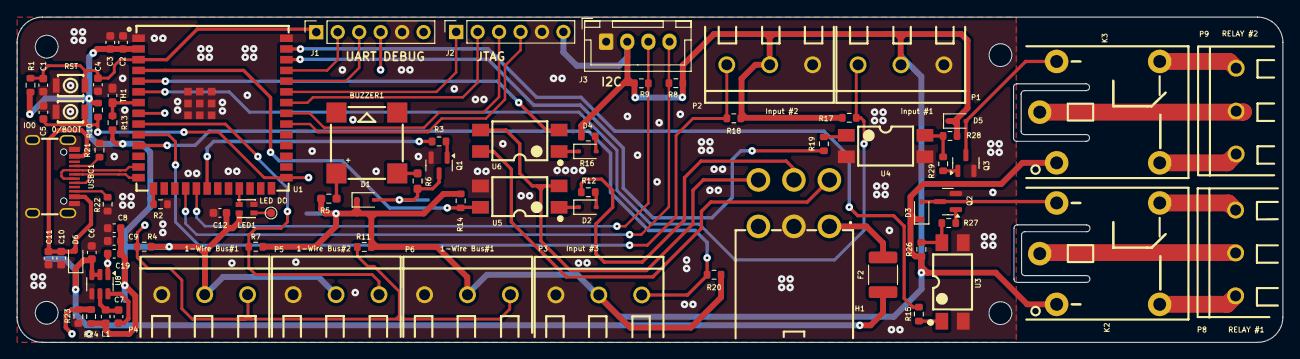
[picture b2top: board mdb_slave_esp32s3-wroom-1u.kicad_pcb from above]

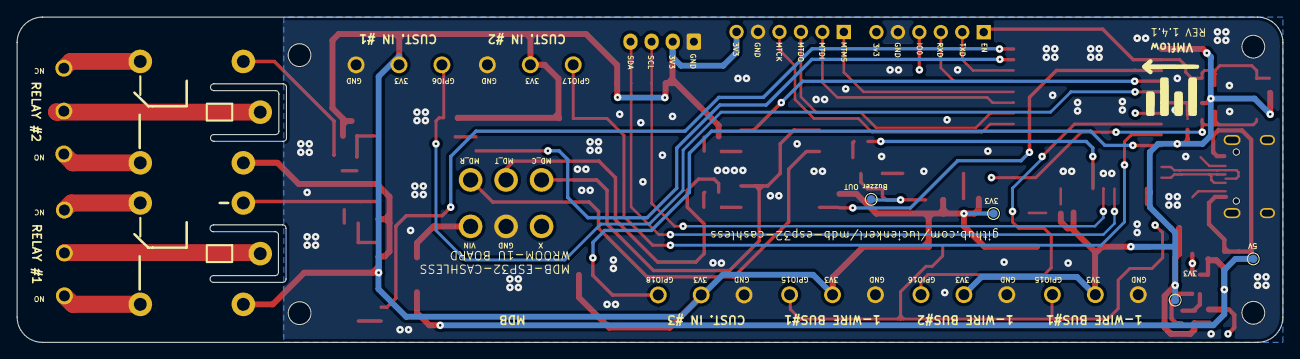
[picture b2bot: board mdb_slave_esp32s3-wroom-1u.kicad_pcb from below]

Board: 4 copper layers, 149.8 x 38.5 mm, 87 parts (4 on the bottom side), 61 nets.

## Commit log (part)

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2025-11-20 url and api key to constants
2025-12-08 index on wifi_password: 7b6ed99 updated WiFi Password to accept longer Passwords
2025-12-09 added github build job
2025-12-09 updated steps url
2025-12-21 index on embeddeds-reload-bug: a703884 fixed bug when pull to refresh used -> the online inficator updated the wrong items
2025-12-24 index on first-iOS-Version: 0382d27 first iOS Version which lists sales
2026-01-06 index on plain_js_html_webui: 010525c code cleanup
2026-01-13 index on main: ec8eaae Moving all in one
2026-02-03 using emqx
2026-02-16 docs(01): research phase 1 foundation and auth
2026-02-16 docs: update STATE.md with Phase 1 plan status
2026-02-16 feat(01-02): create database schema migrations for RBAC
    - Create 001_initial_schema.sql with user_roles and machine_assignments tables
    - Define app_role enum (admin, operator)
    - Enable RLS on both tables
    - Create 002_rls_policies.sql with comprehensive RLS policies
    - Policies cover read access for users and full access for admins
    - Add documentation comments for all tables and policies
2026-02-16 feat(01-02): create auth hook for custom JWT claims
    - Create custom_access_token_hook function to embed user_role in JWT
    - Function queries user_roles table and adds role to claims
    - Defaults to 'operator' if no role found (security by default)
    - Grant necessary permissions to supabase_auth_admin
    - Add comprehensive documentation comments
    - Include verification queries for testing
2026-02-16 feat(01-02): generate TypeScript types from database schema
    - Create database.ts with complete type definitions
    - Define Database interface with Tables, Functions, Enums
    - Add Row, Insert, Update types for user_roles and machine_assignments
    - Include helper types: Tables, TablesInsert, TablesUpdate, Enums
    - Add JSDoc comments documenting each table and type
    - Match types to SQL schema (uuid, text, timestamptz, etc.)
2026-02-16 docs(01-02): complete database schema plan
    - Create SUMMARY.md with execution details
    - Update STATE.md with current position and decisions
    - Document 3 commits with task breakdown
    - Mark 01-02 as complete in phase progress
2026-02-16 docs(01-01): complete project initialization plan
    - Document project structure and configuration
    - Note Node.js version requirement (18+)
    - Record deviations due to environment constraints
    - Add setup instructions for Supabase configuration
2026-02-16 docs(state): update project state after 01-01 completion
    - Mark Wave 1 as complete (2/6 plans in Phase 1)
    - Add key decisions from project initialization
    - Update progress to 10% complete
    - Note Node.js version requirement
    - Set next expected action to Wave 2 execution
2026-02-16 feat(01-04): create useRole composable for JWT role decoding
    - Implement useRole composable using jwt-decode library
    - Decode user_role claim from JWT access_token
    - Provide isAdmin and isOperator computed properties
    - Default to 'operator' role if no claim found
    - Handle decode errors gracefully with null return
    - Support SSR hydration (may return null initially)
2026-02-16 feat(01-03): create authentication composable
    - Add useAuth composable with login, logout, and register functions
    - Implement loading state management with reactive ref
    - Handle errors with try/catch and proper navigation
    - Use readonly to prevent external modification of isLoading
2026-02-16 feat(01-04): create admin middleware for role-based access control
    - Implement admin.ts middleware using useRole composable
    - Check for authenticated session and redirect to login if missing
    - Verify admin role and redirect non-admins to dashboard
    - Can be chained with auth middleware: ['auth', 'admin']
    - Proper TypeScript typing throughout
2026-02-16 feat(01-04): create AppNavigation component with role-based links
    - Implement responsive navigation bar with role-based conditional rendering
    - Admin users see Users and All Machines navigation links
    - Operator users see My Machines navigation link
    - Display user email and role badge (Admin/Operator)
    - Include logout button with proper signOut and navigation
    - Use Tailwind CSS for responsive design and styling
2026-02-16 feat(01-03): create login page with form validation
    - Implement login page with shadcn-vue components
    - Add vee-validate + zod for form validation
    - Email format validation and password minimum length
    - Error handling with clear user feedback
    - Guest middleware prevents authenticated access
    - Loading states on form submission
2026-02-16 feat(01-04): update default layout to use AppNavigation component
    - Replace placeholder navigation with AppNavigation component
    - Add role-based navigation visible on all authenticated pages
    - Use NuxtPage for proper page rendering
    - Complete role-based UI foundation
2026-02-16 docs(01-03): complete authentication UI and flow plan
    - Created SUMMARY.md with all task commits and decisions
    - Updated STATE.md with current position (Plan 01-03 complete)
    - Updated ROADMAP.md progress tracker (3/6 plans complete)
    - Added key decisions for auth patterns and validation approach
    - Verified all files and commits with self-check
2026-02-16 feat(01-05): create user list component
    - Display users from user_roles table
    - Show role badges (Admin/Operator) with color coding
    - Format dates for readability
    - Handle loading and error states
    - Expose refresh method for parent components
2026-02-16 feat(01-05): create user creation modal
    - Form with email, password, and role selection
    - Email and password validation (min 8 chars)
    - Role selection via radio buttons (Admin/Operator)
    - Create user via Supabase signUp
    - Insert role into user_roles table
    - Emit event on successful creation for list refresh
2026-02-16 feat(01-05): create user management page
    - Admin-only page with auth and admin middleware
    - Page header with description
    - Create User button to open modal
    - Integrated UserList component
    - Auto-refresh list after user creation
    - Complete USER-03 requirement implementation
2026-02-16 feat(01-06): create machine assignment list component
    - Display table of operator-machine assignments
    - Fetch from machine_assignments table with operator email join
    - Delete functionality with confirmation
    - Loading and empty states
    - Added table UI components (table, table-header, table-body, table-row, table-head, table-cell)
    - Added minimal toast composable for notifications
2026-02-16 feat(01-06): create machine assignment modal
    - Form with operator selection dropdown and machine ID input
    - Fetch operators from user_roles table where role = 'operator'
    - vee-validate + zod validation (operator_id required, machine_id min 3 chars)
    - Handle unique constraint violations for duplicate assignments
    - Success/error toast notifications
    - Loading states during fetch and submit
2026-02-16 feat(01-06): create operator machine view page
    - Page with auth middleware (accessible to both roles)
    - Fetch machine assignments filtered by operator_id
    - Display machines in card grid layout
    - Show machine ID and assignment date
    - Loading, error, and empty states
    - RLS automatically filters based on user role
2026-02-16 fix: add tsconfig.json for TypeScript configuration
2026-02-16 fix: add vue-tsc and typescript dev dependencies
2026-02-16 fix: correct PostCSS configuration format
2026-02-16 fix: use direct CSS instead of @apply for Tailwind v4 compatibility
2026-02-16 feat: add dark mode toggle with system preference detection
2026-02-27 index on main: 1c5544a feat: add dark mode toggle with system preference detection
2026-03-05 index on main: 8c51e6f added mdb history and debugging support
2026-03-05 index on main: 3f301eb push notification changes
2026-03-10 Initial snapshot
2026-03-10 Before Request: Füge im Dashboard über der His...
2026-04-08 index on main: ddaa3a2 feat(reports): add monthly summary export, VAT breakdown, and payment filters
2026-04-14 index on main: a57ff13 feat(ios): add deals feature — browse retailer offers matched to products
2026-04-23 added native android app, but not feature complete
2026-05-09 feat(analytics): add tray_stockout_events table + trigger
    Tracks per-tray stockout periods for lost-revenue analytics. Trigger
    opens an event on stock positive → 0 transition, closes on 0 →
    positive, with a 5-minute clamp on lost-revenue estimate to absorb
    admin miscount corrections. Includes get_product_velocity_one
    helper (internal-only, REVOKE PUBLIC).
2026-05-09 docs: add tray_stockout_events to schema notes
2026-05-09 feat(analytics): add six analytics RPCs + shared filter helper
    _analytics_filtered_sales handles the WHERE clause; six public RPCs
    (overview, sales_breakdown, products, machines, conversion, operations)
    each return jsonb with version: 1. SECURITY DEFINER, statement_timeout
    10s, REVOKE PUBLIC + GRANT authenticated.
    Three bugs caught and fixed during integration testing:
    - ROUND(float8, int) does not exist in Postgres — added ::numeric cast
2026-05-09 docs: document six analytics RPCs
2026-05-09 feat(analytics): useAnalyticsFilters composable with URL/preset round-trip
2026-05-09 feat(analytics): useAnalyticsData composable with 30s cache
2026-05-09 feat(analytics): useAnalyticsExport with German-locale CSV
2026-05-09 feat(analytics): AnalyticsFilterBar with date/machines/channels/categories/vat filters
2026-05-09 refactor(dashboard): extract AI insights block into CompanyInsights.vue
    No functional change. Phase 3 step 10a per the analytics plan: prepares
    the component for re-use in TabOverview while keeping it on the dashboard
    until Phase 6 deletes the dashboard mount.
2026-05-10 feat(analytics): AnalyticsGeoMap Leaflet bubble map (revenue + conversion)
2026-05-10 feat(analytics): AnalyticsCompareSheet side-by-side machine comparison
2026-05-10 feat(analytics): TabMachines with heatmap toggle + compare + geo map
2026-05-10 feat(analytics): TabOperations with stockouts + refill efficiency + stock-cover
2026-05-10 feat(ios): add SidebarItem.analytics + placeholder AnalyticsRootView
    Wires navigation in MoreView (iPhone) and SidebarNavigationView
    (iPad/Mac). Placeholder content; full implementation in subsequent
    commits.
2026-05-10 feat(ios): AnalyticsRootView adaptive (iPhone picker / iPad split) + filter sheet
2026-05-10 feat(ios): AnalyticsSalesView with dimension picker (machine/product/.../dow)
2026-05-10 feat(ios): AnalyticsProductsView with search/status sub-filters + drill
2026-05-10 feat(ios): AnalyticsMachinesView + AnalyticsCompareView (status/revenue + parallel/stepwise compare)
    Implements Task 6.3 of the Analytics Dashboard plan: per-machine list
    with status indicator, revenue, conversion %, and last-sale gap, plus a
    compare modal that supports up to 4 machines side-by-side on iPad
    (HStack) and stacked on iPhone.
    - AnalyticsMachinesViewModel binds to AnalyticsFilter and calls the
    analytics_machines RPC with the standard 9-param shape.
2026-05-10 refactor(dashboard): remove duplicate AI insights — now lives only in /analytics
    The CompanyInsights component is unchanged and still renders in
    TabOverview. Phase 6 step 18 of the analytics plan.
2026-05-10 docs: document analytics page + composables in CLAUDE.md
2026-05-10 feat(analytics): add /analytics sidebar entry with chart icon
2026-05-11 updated localization file
